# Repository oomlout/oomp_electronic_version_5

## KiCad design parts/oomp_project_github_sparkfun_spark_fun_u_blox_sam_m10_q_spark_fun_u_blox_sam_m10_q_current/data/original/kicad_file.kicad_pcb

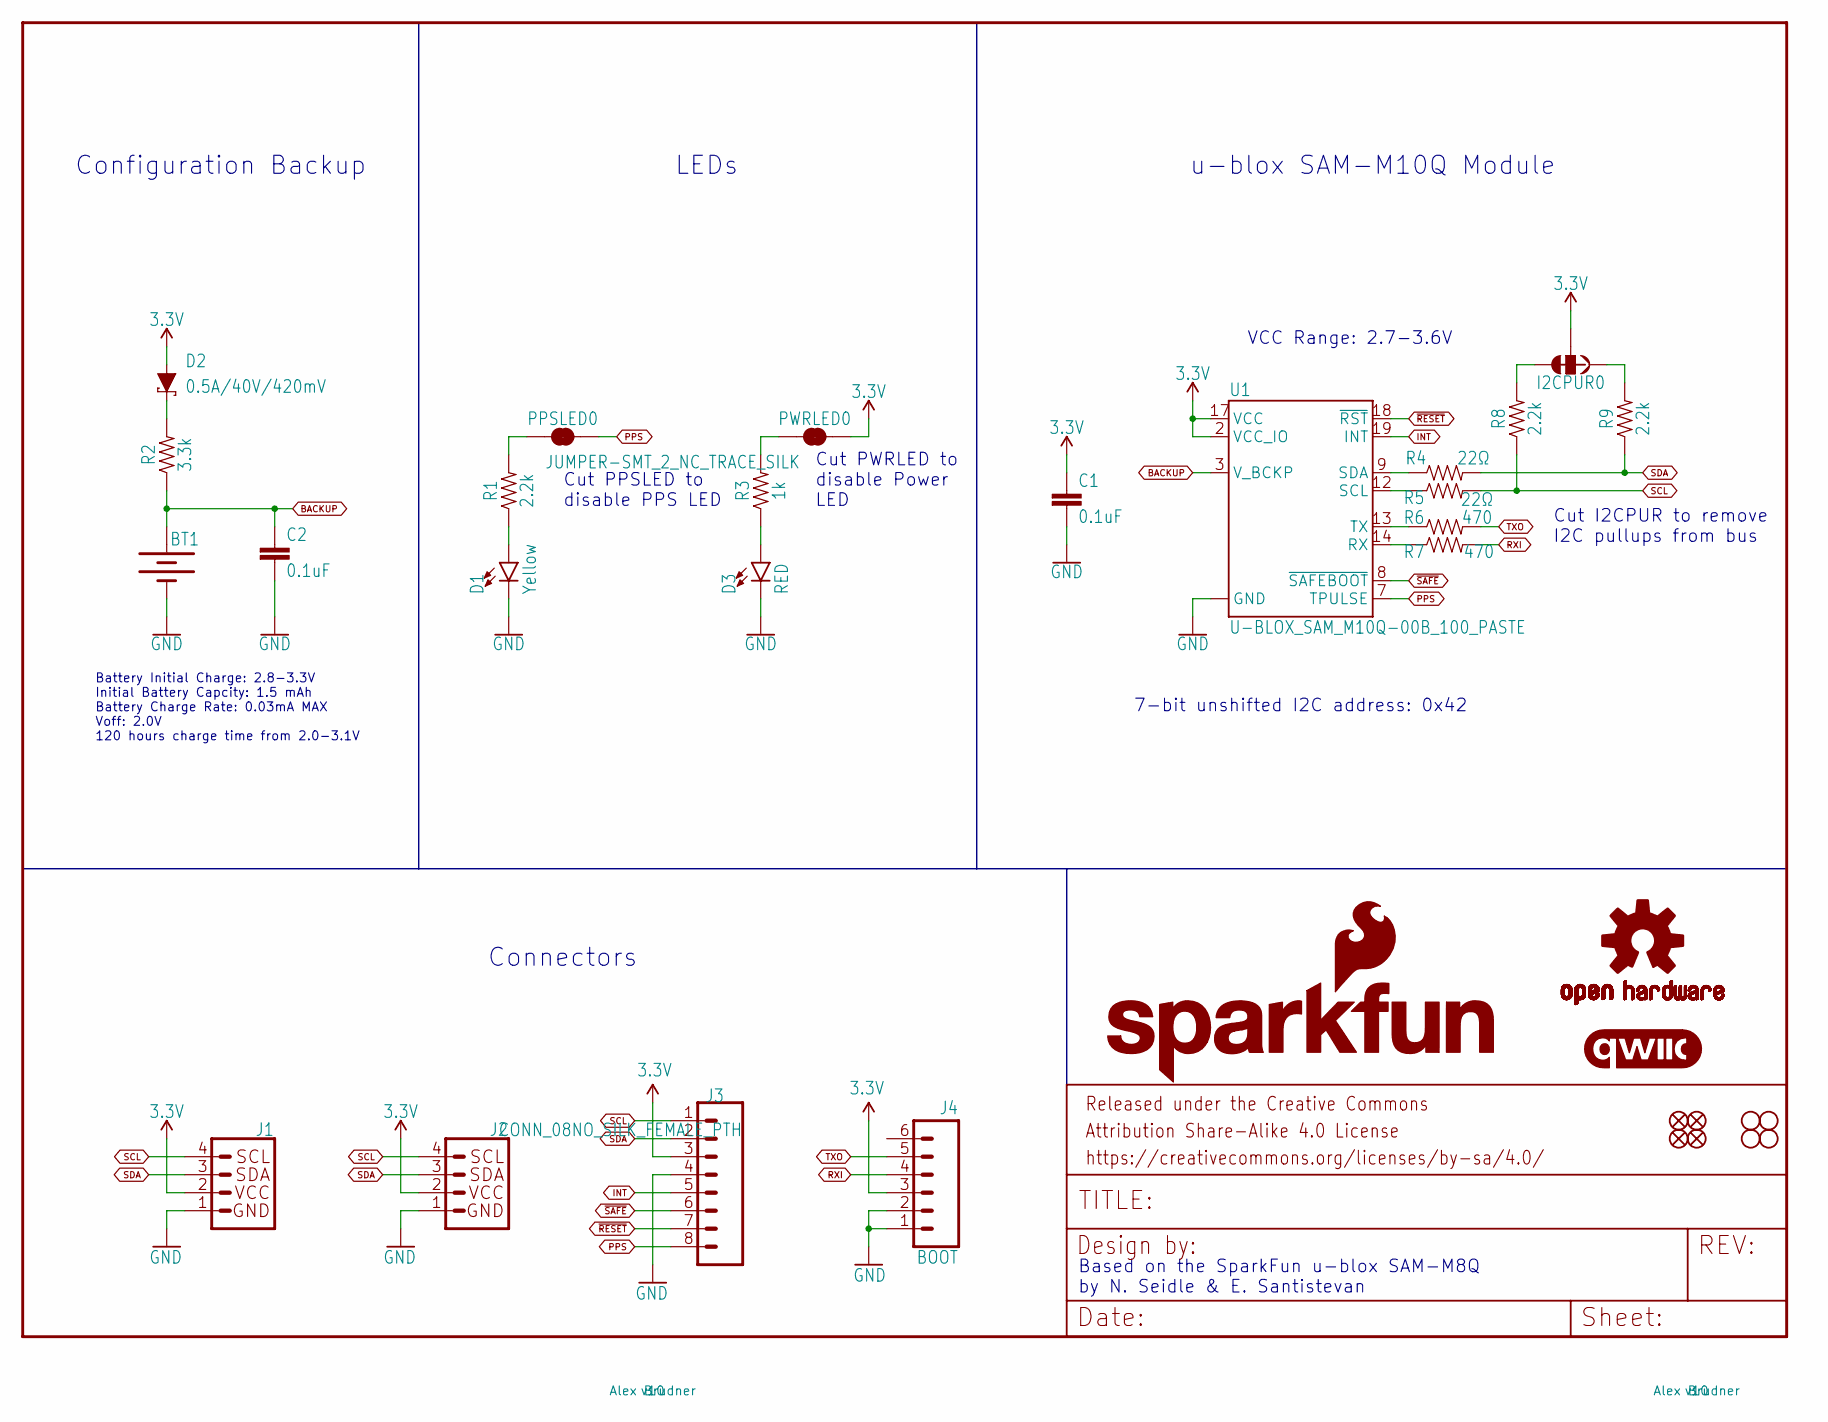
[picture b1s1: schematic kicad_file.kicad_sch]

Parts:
BT1: 6.8MM_COIN_CELL; MS421R_IV03E
C1, C2: 0.1uF; 0603
D1: Yellow; LED-0603
D2: 0.5A/40V/420mV; SOD-323
D3: RED; LED-0603
FD1, FD2, FD3, FD4: FIDUCIALUFIDUCIAL; FIDUCIAL-MICRO
FRAME1: FRAME-LETTER; CREATIVE_COMMONS
H1, H2, H3, H4: STAND-OFF
I2CPUR0: JUMPER-SMT_3_2-NC_TRACE_SILK; SMT-JUMPER_3_2-NC_TRACE_SILK
J1, J2: Qwiic Right Angle; JST04_1MM_RA
J3: CONN_08NO_SILK_FEMALE_PTH; 1X08_NO_SILK
J4: BOOT; 1X06_NO_SILK
LOGO1: OSHW-LOGOM; OSHW-LOGO-M
LOGO2: SFE_LOGO_NAME_FLAME.2_INCH; SFE_LOGO_NAME_FLAME_.2
LOGO3: QWIIC_LOGO_CONNECTOR; QWIIC_5.5MM
PPSLED0: JUMPER-SMT_2_NC_TRACE_SILK; SMT-JUMPER_2_NC_TRACE_SILK
PWRLED0: JUMPER-SMT_2_NC_TRACE_SILK; SMT-JUMPER_2_NC_TRACE_SILK
R1, R8, R9: 2.2k; 0603
R2: 3.3k; 0603
R3: 1k; 0603
R4, R5: 22Ω; 0603
R6, R7: 470; 0603
U1: U-BLOX_SAM_M10Q-00B_100_PASTE; SAM-M10Q_100PASTE

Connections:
3.3V: C1.1, D2.A, I2CPUR0.2, J1.2, J2.2, J3.3, J4.3, PWRLED0.2, U1.2 (VCC_IO), U1.17 (VCC)
BACKUP: BT1.+, C2.1, R2.1, U1.3 (V_BCKP)
GND: BT1.-, C1.2, C2.2, D1.C, D3.C, J1.1, J2.1, J3.4, J4.1, J4.2, U1.1 (GND), U1.4 (GND), U1.5 (GND), U1.6 (GND), U1.10 (GND), U1.11 (GND), U1.15 (GND), U1.16 (GND), U1.20 (GND)
INT: J3.5, U1.19 (INT)
unnamed: PWRLED0.1, R3.2
unnamed: D1.A, R1.1
unnamed: D3.A, R3.1
unnamed: PPSLED0.1, R1.2
unnamed: I2CPUR0.1, R9.2
unnamed: D2.C, R2.2
unnamed: I2CPUR0.3, R8.2
PPS: J3.8, PPSLED0.2, U1.7 (TPULSE)
RXI: J4.4, R7.2
RXLV: R7.1, U1.14 (RX)
SCL: J1.4, J2.4, J3.1, R5.2, R8.1
SCL_LV: R5.1, U1.12 (SCL)
SDA: J1.3, J2.3, J3.2, R4.2, R9.1
SDA_LV: R4.1, U1.9 (SDA)
TXLV: R6.1, U1.13 (TX)
TXO: J4.5, R6.2
~RESET: J3.7, U1.18 (~RST)
~SAFE: J3.6, U1.8 (~SAFEBOOT)

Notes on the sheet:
Battery Initial Charge: 2.8-3.3V Initial Battery Capcity: 1.5 mAh Battery Charge Rate: 0.03mA MAX Voff: 2.0V 120 hours charge time from 2.0-3.1V
Cut PPSLED to disable PPS LED
Cut PWRLED to disable Power LED
VCC Range: 2.7-3.6V
Based on the SparkFun u-blox SAM-M8Q by N. Seidle & E. Santistevan
u-blox SAM-M10Q Module
Cut I2CPUR to remove I2C pullups from bus
LEDs
Configuration Backup
7-bit unshifted I2C address: 0x42
Connectors

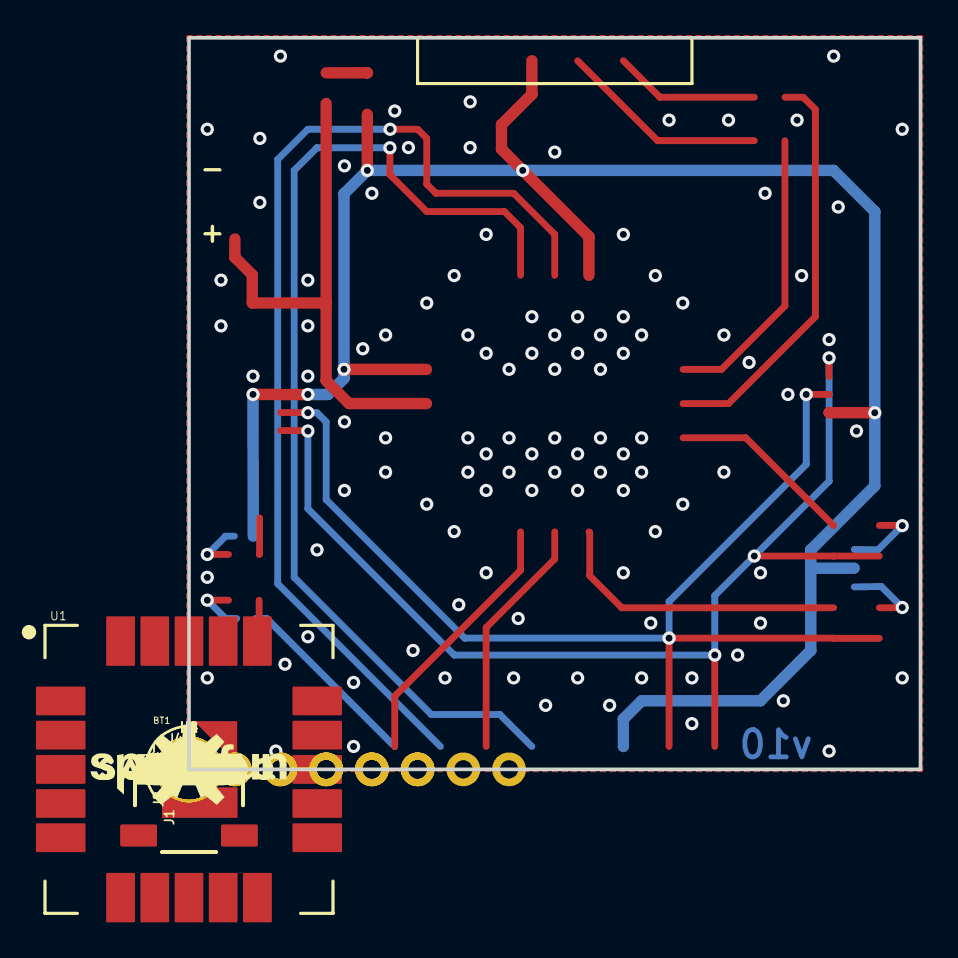
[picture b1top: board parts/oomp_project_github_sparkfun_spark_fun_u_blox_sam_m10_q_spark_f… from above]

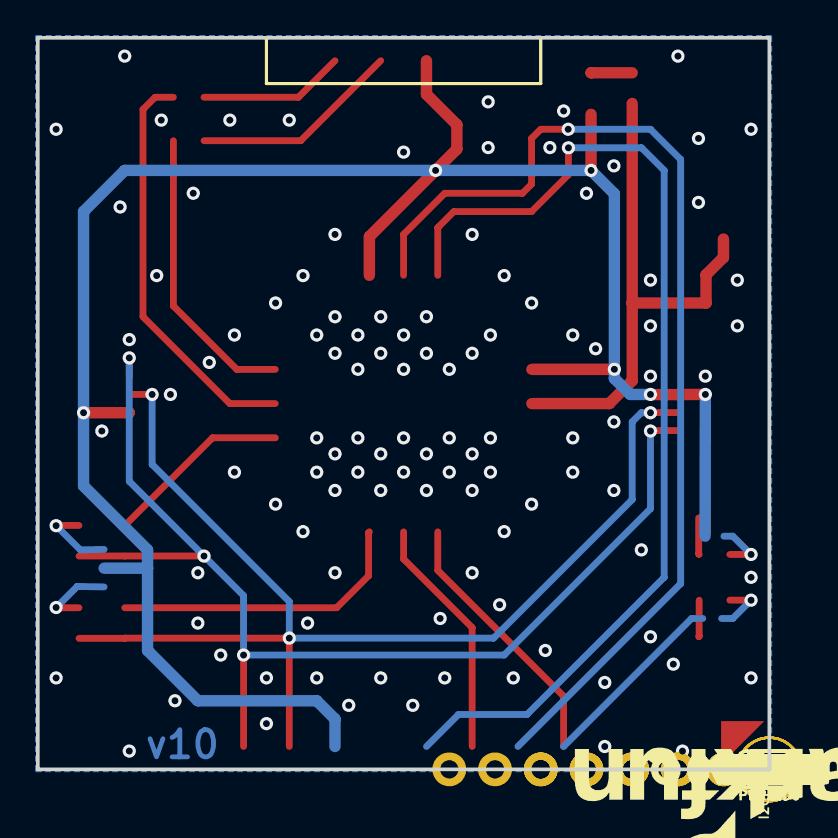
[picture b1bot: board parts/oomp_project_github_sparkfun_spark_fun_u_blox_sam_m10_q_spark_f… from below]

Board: 2 copper layers, 40.6 x 40.6 mm, 76 parts (26 on the bottom side), 22 nets.

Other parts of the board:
U$1: SFE_LOGO_FLAME_STOP_.1
U$2: SAM#M10Q11
U$3, U$4: BLK4
U$5, U$6: GRN5
U$7, U$8: UART7
U$9: PPS9
U$10: PWR10
U$11, U$12: #TX#12
U$13, U$14: #RX#13
U$15, U$16, U$22, U$23: #3V3#0
U$17, U$20: #GND#4
U$18: U#BLOX11
U$19, U$21: #GND#5
U$24, U$25: #SCL#6
U$26, U$27: #SDA#7
U$28, U$29: #INT#8
U$30, U$33: ##RST##15
U$31: SFE_LOGO_NAME_.1
U$32: SAM#M10Q12
U$34, U$35: #PPS#13
U$36, U$37: ##SAFE##16
U$38: U#BLOX12
U$40: #PPSLED#0
U$41: #I2CPUR#0
U$42: #PWRLED#0

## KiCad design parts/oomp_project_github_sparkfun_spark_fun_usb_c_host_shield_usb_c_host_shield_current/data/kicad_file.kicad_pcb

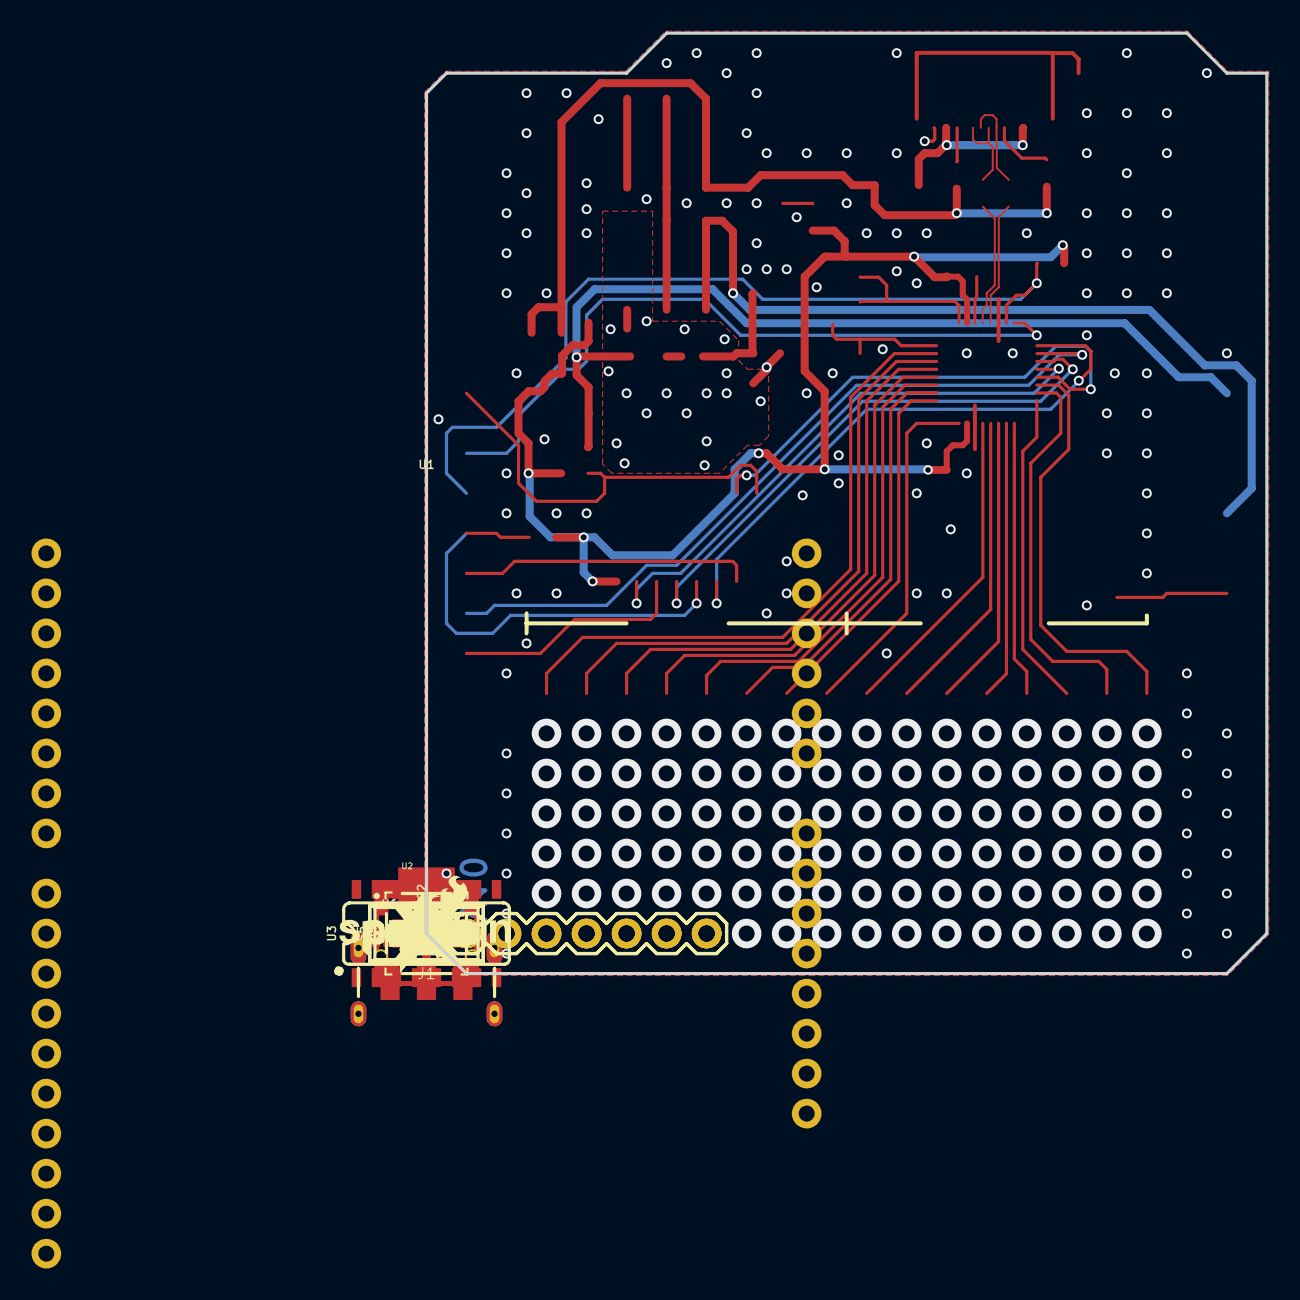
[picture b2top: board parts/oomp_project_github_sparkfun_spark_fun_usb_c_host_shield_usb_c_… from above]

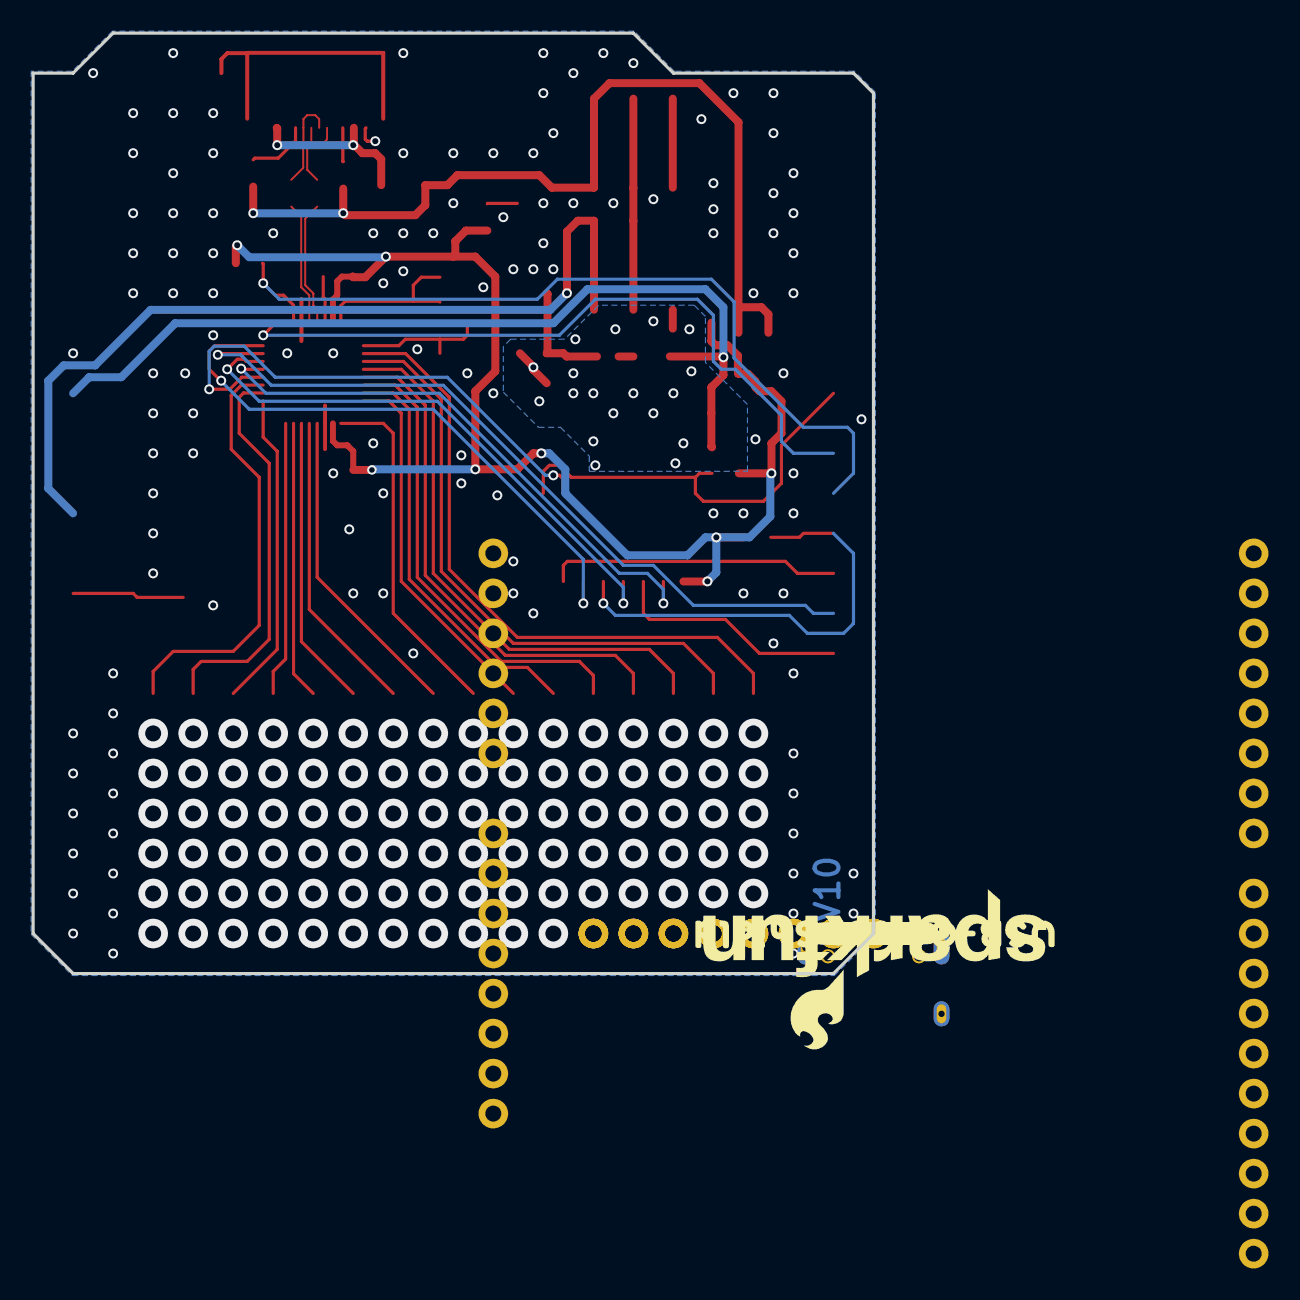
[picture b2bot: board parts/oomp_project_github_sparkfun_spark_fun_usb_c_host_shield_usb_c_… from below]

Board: 2 copper layers, 53.3 x 59.7 mm, 139 parts (35 on the bottom side), 49 nets.

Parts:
C1, C2, C3, C4, C5: 0.1uF; 0603
C6, C7: 10uF; EIA3216
C8: 10uF; 0603
C9, C10: 18pF; 0603
C11: 10uF; 0805
D1: RED; LED-0603
F1: 6V/0.75A; 1206
FD1, FD2, FD3, FD4: FIDUCIALUFIDUCIAL; FIDUCIAL-MICRO
FRAME1: FRAME-LETTER; CREATIVE_COMMONS
J1: USB-C; USB-C-16P-2LAYER-PADS
J2: GPIN; 1X08
J3: GPOUT; 1X08
LOGO1: OSHW-LOGOM; OSHW-LOGO-M
LOGO2: SFE_LOGO_NAME_FLAME.1_INCH; SFE_LOGO_NAME_FLAME_.1
LOGO3: SFE_LOGO_NAME_FLAME.2_INCH; SFE_LOGO_NAME_FLAME_.2
LOGO7: REVISION
R1: 1k; 0603
R2, R3: 33; 0603
R4, R5: 10k; 0603
R6: 2.2k; 0603
R7: 715; 0603
R8: 240; 0603
R9, R10: 56k; 0603
S2: MOMENTARY-SWITCH-SPST-SMD-5.2MM-TALL; TACTILE_SWITCH_SMD_5.2MM
S4: Power Select; SWITCH_DPDT_SMD_AYZ0202
S5: Main Power; SWITCH_DPDT_SMD_AYZ0202
SHLD0: JUMPER-SMT_2_NC_TRACE_SILK; SMT-JUMPER_2_NC_TRACE_SILK
U1: ARDUINO_UNO_R3_SHIELDNOLABELS; UNO_R3_SHIELD_NOLABELS
U2: LM1117; SOT223
U3: 74HC4050; SO16
U5: MAX3421; TQFP32
U6: 3.3V/150mA; SOT23-5
U$1: 5V6
U$2: POWER23
U$3: GPIN42
U$4: SFE_LOGO_FLAME_.2
U$5: ON26
U$6: RESET25
U$7: OFF27
U$8: ANALOG_IN28
U$9: USB#C_HOST_SHIELD32
U$10: POWER11
U$11: SHLD#33
U$12: VIN7
U$13: SELECT12
U$14: POWER38
U$15: MAIN40
U$16: GPOUT44
U$17, U$29: 045
U$18, U$30: 146
U$19, U$31: 2147
U$20, U$32: 32148
U$21, U$22: 4332150
U$23, U$25: 54332151
U$24, U$26: 654332152
U$27, U$28: 7654332153
U$33: #5V4
U$34: VIN6
U$35, U$51: GND131211109817654321131211211109876543260
U$36: SDA131211109817654321131211211109876543261
U$37: GND131211211109876543229
U$38, U$55: 21131211211109876543246
U$39, U$56: 321131211211109876543247
U$40, U$57: 4321131211211109876543248
U$41, U$58: 54321131211211109876543249
U$42: 654321131211211109876543250
U$43: 7654321131211211109876543251
U$44: 17654321131211211109876543252
U$45: 017654321131211211109876543253
U$46: 9817654321131211211109876543255
U$47: 109817654321131211211109876543256
U$48: 11109817654321131211211109876543257
U$49: 1211109817654321131211211109876543258
U$50: 131211109817654321131211211109876543259
U$52: AREF131211211109876543230
U$53: SCL131211109817654321131211211109876543262
U$54: IOREF131211109817654321131211211109876543264
U$59: 817654321131211211109876543254
U$60: RST131211109817654321131211211109876543265
U$61: #_4#6
U$62: #3#3V4
U$63: #_5#6
U$64: RX13
U$65: TX1131211211109876543245
U$66: #_3#6
U$67: #_2#6
U$68: #_1#6
U$69: #_0#6
U$70: #_VIN#6
U$71, U$72: #_GND#7
U$73: #_#5V#8
U$74: #_#3#3V#8
U$75: #_RST#8
U$76: #_IOREF#9
U$77: #RX_#10
U$78: #TX_#11
U$79: #2_#12
U$80: #3_#12
U$81: #4_#12
U$82: #5_#12
U$83: #6_#12
U$84: #7#RESET_#12
U$85: #8#GPX_#12
U$86: #9#INT_#12
U$87: #10#CS_#12
U$88: #11#PICO_#12
U$89: #12#POCI_#12
U$90: #13#SCK_#13
U$92: #GND#21
U$93: #SDA#18
U$94: #SCL#19
U$95: #AREF#20
Y1: 12.0mhZ; CRYSTAL-SMD-2X2.5MM

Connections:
3.3V: C4.1, C5.1, C8.1, R1.2, R4.2, R5.2, R6.2, U3.1, U5.2, U5.23, U6.5
5V: S4.1, S4.4, U1.5V
CC1: J1.A5, R9.1
CC2: J1.B5, R10.1
CS: R5.1, U1.D10, U3.5
CS-IN: U3.4, U5.14
D_N: J1.A7, J1.B7, R2.1
D_P: J1.A6, J1.B6, R3.1
GND: C1.2, C2.2, C3.2, C4.2, C5.2, C6.-, C7.-, C8.2, C9.2, C10.2, C11.2, D1.C, J1.GND, J1.GND2, R7.1, S2.1, SHLD0.1, U1.GND@0, U1.GND@1, U1.GND@2, U3.8, U5.3, U5.19, U6.2
GPIN0: J2.1, U5.26
GPIN1: J2.2, U5.27
GPIN2: J2.3, U5.28
GPIN3: J2.4, U5.29
GPIN4: J2.5, U5.30
GPIN5: J2.6, U5.31
GPIN6: J2.7, U5.32
GPIN7: J2.8, U5.1
GPOUT0: J3.1, U5.4
GPOUT1: J3.2, U5.5
GPOUT2: J3.3, U5.6
GPOUT3: J3.4, U5.7
GPOUT4: J3.5, U5.8
GPOUT5: J3.6, U5.9
GPOUT6: J3.7, U5.10
GPOUT7: J3.8, U5.11
GPX: U1.D8, U5.17
INT: R6.1, U1.D9, U5.18
MAX_D_N: R2.2, U5.20
MAX_D_P: R3.2, U5.21
unnamed: S2.3, U1.RES
unnamed: S4.2, S4.5, S5.2, S5.5
unnamed: C11.1, R7.2, R8.1, U2.1
unnamed: S5.1, S5.4
unnamed: C2.1, C7.+, R8.2, S4.3, S4.6, U2.2, U2.4
unnamed: D1.A, R1.1
unnamed: J1.SHLD1, J1.SHLD2, J1.SHLD3, J1.SHLD4, SHLD0.2
PICO: U1.D11, U3.7
PICO-IN: U3.6, U5.16
POCI: U1.D12, U5.15
RESET: R4.1, U1.D7, U3.9
RESET-IN: U3.10, U5.12
SCK: U1.D13, U3.3
SCK-IN: U3.2, U5.13
VBCOMP: C3.1, U5.22
VBUS: F1.1, J1.VBUS1, J1.VBUS2
VDD: F1.2, R9.2, R10.2, S5.3, S5.6, U6.1, U6.3
VIN: C1.1, C6.+, U1.VIN, U2.3
XI: C10.1, U5.24, Y1.P3
XO: C9.1, U5.25, Y1.P1

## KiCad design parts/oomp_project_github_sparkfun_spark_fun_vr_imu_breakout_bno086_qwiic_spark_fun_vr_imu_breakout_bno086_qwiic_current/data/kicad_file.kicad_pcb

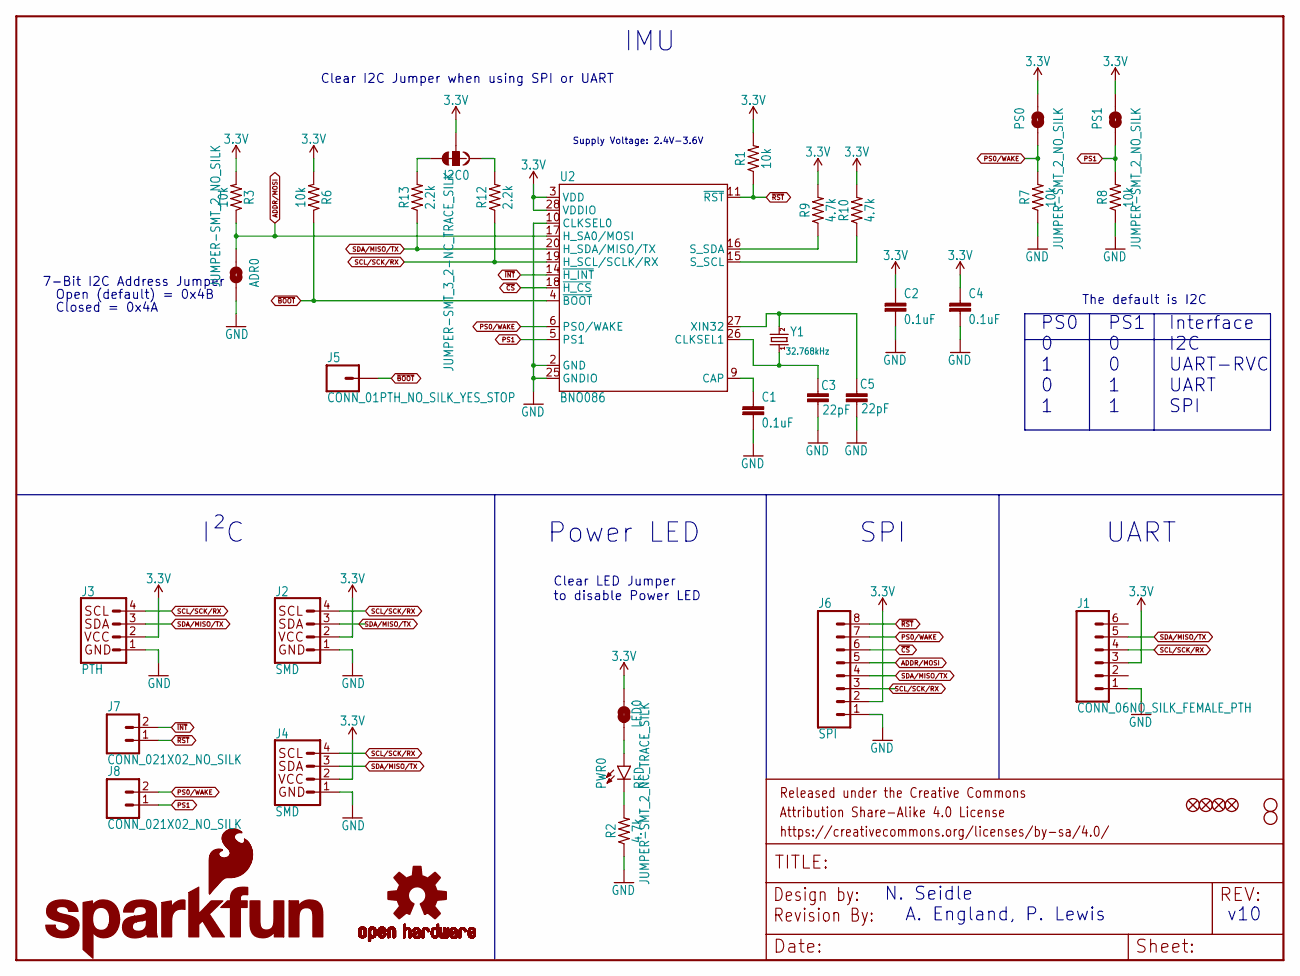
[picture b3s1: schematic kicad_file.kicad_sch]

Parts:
ADR0: JUMPER-SMT_2_NO_SILK; SMT-JUMPER_2_NO_SILK
C1, C2, C4: 0.1uF; 0603
C3, C5: 22pF; 0603
FRAME1: FRAME-LETTER; CREATIVE_COMMONS
I2C0: JUMPER-SMT_3_2-NC_TRACE_SILK; SMT-JUMPER_3_2-NC_TRACE_SILK
J1: CONN_06NO_SILK_FEMALE_PTH; 1X06_NO_SILK
J2, J4: SMD; JST04_1MM_RA
J3: PTH; 1X04_NO_SILK
J5: CONN_01PTH_NO_SILK_YES_STOP; 1X01_NO_SILK
J6: SPI; 1X08_NO_SILK
J7, J8: CONN_021X02_NO_SILK; 1X02_NO_SILK
JP1, JP2, JP5, JP6: FIDUCIALUFIDUCIAL; FIDUCIAL-MICRO
JP3, JP4: STAND-OFF
LED0: JUMPER-SMT_2_NC_TRACE_SILK; SMT-JUMPER_2_NC_TRACE_SILK
LOGO1: OSHW-LOGOMINI; OSHW-LOGO-MINI
LOGO2: REVISION
LOGO4: SFE_LOGO_FLAME.2_INCH; SFE_LOGO_FLAME_.2
LOGO5: SFE_LOGO_NAME_FLAME.1_INCH; SFE_LOGO_NAME_FLAME_.1
PS0, PS1: JUMPER-SMT_2_NO_SILK; SMT-JUMPER_2_NO_SILK
PWR0: RED; LED-0603
R1, R3, R6, R7, R8: 10k; 0603
R2, R9, R10: 4.7k; 0603
R12, R13: 2.2k; 0603
U2: BNO086; LGA-28
Y1: 32.768kHz; CRYSTAL-SMD-3.2X1.5MM

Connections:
3.3V: C2.1, C4.1, I2C0.2, J1.3, J2.2, J3.2, J4.2, J6.2, LED0.1, PS0.1, PS1.1, R1.2, R3.2, R6.2, R9.2, R10.2, U2.3 (VDD), U2.28 (VDDIO)
ADDR/MOSI: ADR0.2, J6.5, R3.1, U2.17 (H_SA0/MOSI)
CAP: C1.1, U2.9 (CAP)
GND: ADR0.1, C1.2, C2.2, C3.2, C4.2, C5.2, J1.1, J2.1, J3.1, J4.1, J6.1, R2.1, R7.1, R8.1, U2.2 (GND), U2.10 (CLKSEL0), U2.25 (GNDIO)
unnamed: C5.1, U2.27 (XIN32), Y1.P$2 (2)
unnamed: C3.1, U2.26 (CLKSEL1), Y1.P$1 (1)
unnamed: PWR0.C, R2.2
unnamed: LED0.2, PWR0.A
PS0/WAKE: J6.7, J8.2, PS0.2, R7.2, U2.6 (PS0/WAKE)
PS1: J8.1, PS1.2, R8.2, U2.5 (PS1)
SCL/SCK/RX: J1.4, J2.4, J3.4, J4.4, J6.3, R12.1, U2.19 (H_SCL/SCLK/RX)
SCL_PU: I2C0.1, R12.2
SDA/MISO/TX: J1.5, J2.3, J3.3, J4.3, J6.4, R13.1, U2.20 (H_SDA/MISO/TX)
SDA_PU: I2C0.3, R13.2
S_SCL: R10.1, U2.15 (S_SCL)
S_SDA: R9.1, U2.16 (S_SDA)
~BOOT: J5.1, R6.1, U2.4 (~BOOT)
~CS: J6.6, U2.18 (~H_CS)
~INT: J7.2, U2.14 (~H_INT)
~RST: J6.8, J7.1, R1.1, U2.11 (~RST)

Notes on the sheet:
IMU
Supply Voltage: 2.4V-3.6V
Interface I2C UART-RVC UART SPI
I C
The default is I2C
Open (default) = 0x4B
A. England, P. Lewis
SPI
PS1 0 0 1 1
N. Seidle
Power LED
v10
PS0 0 1 0 1
Clear I2C Jumper when using SPI or UART
Clear LED Jumper to disable Power LED
UART
7-Bit I2C Address Jumper
Closed = 0x4A

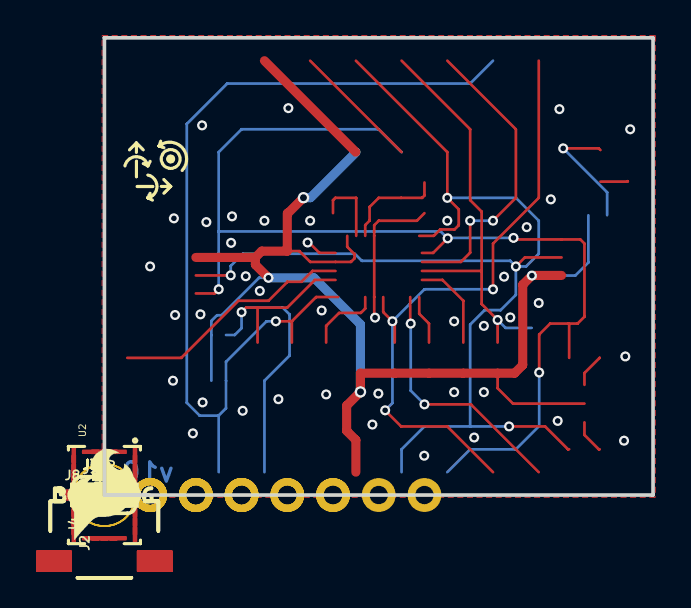
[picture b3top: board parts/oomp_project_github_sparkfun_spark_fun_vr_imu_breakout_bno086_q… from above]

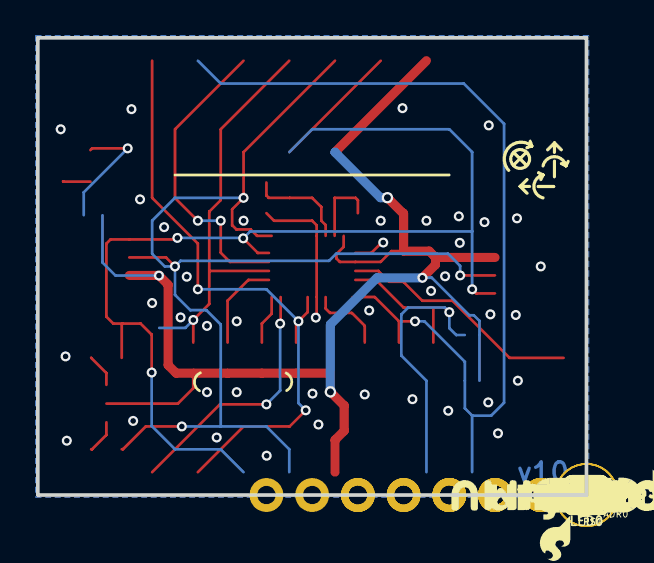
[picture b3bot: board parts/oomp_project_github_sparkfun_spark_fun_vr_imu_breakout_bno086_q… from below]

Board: 2 copper layers, 30.5 x 25.4 mm, 102 parts (43 on the bottom side), 20 nets.

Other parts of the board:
U$1: #I2C#874
U$2: BLK889
U$3, U$25: X878
U$4: ##INT##6
U$5: ##RST##5
U$6, U$10: Y879
U$7, U$15: Z880
U$8: #SCL#4
U$9, U$16: #GND#2
U$11: #SCK#882
U$12: #SO#867
U$13: #SI#868
U$14: #SDA#3
U$17: ##CS##870
U$18: ##CS##885
U$19: ##RST##872
U$20: ##RST##887
U$21: RXI891
U$22: TXO892
U$23: #PS0#874
U$24: BNO0861
U$26: #LED#0
U$27, U$46: #3V3#874
U$28: OPEN#0X4B0
U$29: QWIIC_4MM
U$30: #ADR#894
U$31: IMU862
U$32, U$45: #GND#864
U$33: #PS1#1
U$34: #PS0#2
U$35: #PS1#895
U$36: #3V3#865
U$37: #SCK#866
U$38: ##WAK##871
U$39: #3V3#882
U$40: 3V3891
U$41: GRN890
U$42: #PWR#873
U$43: #PS1#874
U$44: UART881
U$47: #SDA#874
U$48: #SCL#875
U$49: #BOOT#888
U$50: ##RST##876
U$51: ##INT##877
U$52: QWIIC_6MM
U$53: ##WAK##886
U$54: BNO086_IMU881
U$55: #SO#883
U$56: #SI#884
U$57: #PS0#895
U$58: CLOSED#0X4A0
U$59: ORDERING_INSTRUCTIONS
U$61: DEFAULT0

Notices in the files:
parts/oomp_project_github_sparkfun_spark_fun_u_blox_sam_m10_q_spark_fun_u_blox_sam_m10_q_current/data/original/kicad_file.kicad_sch:
Released under the Creative Commons
https://creativecommons.org/licenses/by-sa/4.0
parts and their libraries:
Released under the Creative Commons Attribution Share-Alike 4.0 License
